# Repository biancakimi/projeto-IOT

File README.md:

# SmartGreenhouse LoRa — Sistema IoT de Monitoramento e Automação de Estufa Remota

-blue?style=flat-square&logo=espressif)

Sistema completo de **Internet das Coisas (IoT)** para monitoramento microclimático e controle automatizado de uma **estufa agrícola remota** sem cobertura Wi-Fi local. O projeto utiliza dois microcontroladores **ESP32-S3 LoRa 915 MHz (Heltec WiFi LoRa 32 V3)** operando em arquitetura *Nó Sensor/Atuador (ESP 1) $\leftrightarrow$ Gateway (ESP 2)*, integrados em tempo real via **Broker MQTT (`broker.emqx.io`)**, **API Serverless na Vercel (`/api/historico`)**, fluxos de automação em **Node-RED**, persistência histórica em **Banco de Dados Neon PostgreSQL** e uma **Aplicação Web de Gerenciamento Remoto**.

> **Universidade Federal de São Paulo (UNIFESP)** — Instituto de Ciência e Tecnologia (ICT - SJC)  
> **Disciplina:** Internet das Coisas (IdC) — Prof. Dr. Gabriel de Freitas Fernandes

---

## Sumário

1. [Visão Geral do Sistema](#visão-geral-do-sistema)
2. [Arquitetura de Comunicação](#arquitetura-de-comunicação)
3. [Funcionalidades e Modos de Operação](#funcionalidades-e-modos-de-operação)
   - [1. Modo Automático (Controle Local Resiliente)](#1-modo-automático-controle-local-resiliente)
   - [2. Modo Manual (Override Remoto pelo Site / Node-RED)](#2-modo-manual-override-remoto-pelo-site--node-red)
4. [Hardware e Pinagem (Nó Estufa — Heltec V3)](#hardware-e-pinagem-nó-estufa--heltec-v3)
5. [Protocolo de Mensagens (LoRa & MQTT)](#protocolo-de-mensagens-lora--mqtt)
   - [Pacotes LoRa (915 MHz)](#pacotes-lora-915-mhz)
   - [Tópicos MQTT](#tópicos-mqtt)
6. [Estrutura do Repositório](#estrutura-do-repositório)
7. [Fluxo de Trabalho Git e Automação de Pull Requests](#fluxo-de-trabalho-git-e-automação-de-pull-requests)
8. [Como Executar o Projeto](#como-executar-o-projeto)
9. [Integrantes e Divisão de Responsabilidades](#integrantes-e-divisão-de-responsabilidades)

---

## Visão Geral do Sistema

Estufas de cultivo frequentemente estão afastadas de pontos de acesso Wi-Fi. Para contornar essa limitação e garantir alta confiabilidade, o **SmartGreenhouse LoRa** organiza a solução em três camadas:

1. **Nó Estufa — ESP 1 (ESP32-S3 Heltec WiFi LoRa 32 V3 — Remoto):** Instalado na estufa sem necessidade de internet local. Realiza a leitura contínua de **luminosidade (LDR no GPIO 4)** e **temperatura e umidade do ar (DHT11 no GPIO 5)**, exibe o diagnóstico no **Display OLED SSD1306 integrado**, controla o ângulo da **persiana via 1 servomotor (GPIO 6)**, aciona **1 Módulo Relé de 4 Canais 5V (nos GPIOs 47, 48, 33 e 34)** (Ventoinha 5V de exaustão, iluminação de cultivo, bomba de irrigação e aquecedor) e sinaliza status localmente (**LEDs Verde/Vermelho com resistores de 1 kΩ e Buzzer**). Transmite telemetria via **LoRa 915 MHz** a cada 5s (e imediatamente após executar qualquer comando recebido do ESP 2) e mantém controle autônomo local (*fail-safe*).
2. **Nó Gateway — ESP 2 (ESP32-S3 Heltec WiFi LoRa 32 V3 — Central):** Localizado na sede com conexão Wi-Fi 2.4 GHz. Recebe os pacotes LoRa em 915 MHz vindos do ESP 1 (via transceptor Semtech SX1262), afere a qualidade do enlace de rádio (`RSSI` em dBm e `SNR` em dB) e encaminha os dados simultaneamente para o **Broker MQTT (`broker.emqx.io`)** e via **HTTPS POST para a API Serverless da Vercel (`/api/historico`)**. No sentido inverso, recebe ordens enviadas pelo Site Web ou Node-RED e as transmite imediatamente via **LoRa 915 MHz** para o ESP 1. Conta ainda com portal web local (`Gateway_LoRa_V3` $\rightarrow$ `http://192.168.4.1`) para configuração dinâmica de Wi-Fi/MQTT e suporte a **atualização remota de firmware (ArduinoOTA)**.
3. **Nuvem, Banco de Dados e Site Web:**
   * **API Serverless Vercel (`api/historico.js`) + Neon PostgreSQL:** Cria automaticamente as tabelas `historico_estufa` e `comandos_estufa`, armazena a série temporal completa de leituras/estados e enfileira comandos remotos para o Gateway.
   * **Node-RED (`nuvem_nodered/flows_estufa.json`):** Orquestra a ingestão dos pacotes MQTT, formata payloads para o banco SQL e disponibiliza botões de injeção de comandos.
   * **Site Web de Controle (`web/`):** Interface web responsiva hospedada na **Vercel** (e executável localmente), conectada em tempo real via **MQTT over WebSockets (`wss://broker.emqx.io:8084/mqtt`)** e integrada à API `/api/historico` para exibição de gráficos históricos (Chart.js) e tabela de registros.

---

## Arquitetura de Comunicação

```mermaid
flowchart LR
    subgraph Estufa["Nó Estufa (Heltec V3 Remota)"]
        direction TB
        LDR["Sensor LDR (GPIO 4)"] --> ESP_EST["ESP32-S3 Heltec V3\n+ OLED SSD1306"]
        DHT["Sensor DHT11 (GPIO 5)"] --> ESP_EST
        ESP_EST --> SERVO["1x Servomotor\n(Persiana 0°–180° - GPIO 6)"]
        ESP_EST --> RELES["1x Módulo Relé 4 Canais (5V)\n(CH1 Ventoinha P47 | CH2 Iluminação P48 |\nCH3 Irrigação P33 | CH4 Aquecedor P34)"]
        ESP_EST --> ALARME["LEDs Status + Buzzer (GPIO 40, 41, 42)"]
    end

    subgraph Enlace["Rádio LoRa 915 MHz"]
        RF(("Semtech SX1262\nP2P Bidirecional"))
    end

    subgraph Gateway["ESP 2: Nó Gateway (Heltec V3 Central)"]
        ESP_GW["ESP32-S3 Heltec V3\n(Bridge LoRa <-> MQTT & HTTPS\n+ Portal 192.168.4.1 + OTA)"]
    end

    subgraph Cloud["Nuvem & Gerenciamento Web"]
        BROKER["Broker MQTT EMQX\n(TCP 1883 / WSS 8084)"]
        API["Vercel Serverless API\n(/api/historico)"]
        NODERED["Node-RED\n(Ingestão + Automação)"]
        DB[("Neon PostgreSQL\n(Histórico em Nuvem)")]
        SITE["Site Web Responsivo\n(Vercel + Chart.js)"]
    end

    ESP_EST <==>|"Telemetria & Ordens"| RF
    RF <==>|"RSSI / SNR"| ESP_GW
    ESP_GW <==>|"Wi-Fi (MQTT)"| BROKER
    ESP_GW <==>|"HTTPS POST"| API
    API <==>|"SQL"| DB
    BROKER <==>|"Pub/Sub"| NODERED
    BROKER <==>|"WebSockets (WSS)"| SITE
    API <==>|"Histórico & Comandos"| SITE
```

---

## Funcionalidades e Modos de Operação

### 1. Modo Automático (Controle Local Resiliente)
O Nó Estufa avalia continuamente os sensores a cada ciclo curto (~600 ms para LDR e 2 s para DHT11) e atua autonomamente:

* **Controle do Servomotor da Persiana (GPIO 6) em Resposta à Luz (LDR):**
  * **Escuro / Tampando o LDR (`Luz < 25%`):** Persiana fecha em **`0°` (Fechada)** para isolamento térmico e **LIGA o Relé 2 (Iluminação de Cultivo)** para suplementação luminosa.
  * **Luz Ambiente Normal (`25% <= Luz <= 75%`):** Persiana abre em **`90°` (Aberta)** para máximo aproveitamento da luz solar e ventilação natural, **DESLIGANDO o Relé 2**.
  * **Sol Muito Forte / Lanterna no LDR (`Luz > 75%`):** Persiana inclina para **`160°` (Sombreamento)** para proteger as plantas contra insolação excessiva e queima de folhas.
* **Controle do Módulo Relé de 4 Canais 5V (Lado do Pino 47):**
  * **Canal 1 (`IN1`) — Ventoinha 5V (Exaustor / Refrigeração):** Liga quando `Temperatura > 28 °C` ou `Umidade > 80%`.
  * **Canal 2 (`IN2`) — Iluminação Artificial (Cultivo):** Liga automaticamente quando `Luz < 25%`.
  * **Canal 3 (`IN3`) — Bomba de Irrigação / Nebulização:** Liga quando `Umidade < 45%`.
  * **Canal 4 (`IN4`) — Aquecedor Térmico:** Liga quando `Temperatura < 18 °C`.
* **Alarme Audiovisual Local (Buzzer + LEDs):**
  * **LED Verde (GPIO 41):** Aceso contínuo durante operação normal.
  * **LED Vermelho (GPIO 40) + Buzzer (GPIO 42):** Acionados em caso de emergência climática (`Temperatura >= 35 °C`), forçando a Ventoinha (Relé 1) a ligar e transmitindo status de alerta via LoRa/MQTT.
  * O Buzzer também emite bipes curtos de aviso ao movimentar a persiana.

### 2. Modo Manual (Override Remoto pelo Site / Node-RED)
Através do painel web ou do Node-RED, o operador pode assumir o controle a qualquer momento:
* Ajuste do ângulo da persiana ($0^\circ$ a $180^\circ$) por *slider* ou atalhos rápidos (*Fechar 0°*, *Meia-Luz 45°*, *Abrir 90°*, *Sombra 160°*).
* Acionamento manual e individual dos 4 Relés (Ventoinha, Iluminação de Cultivo, Irrigação, Aquecedor).
* Inversão rápida da lógica de disparo dos relés (`Ativo em HIGH` $\leftrightarrow$ `Ativo em LOW`).
* Silenciamento temporário (*Mute*) ou teste manual do Buzzer.
* Reprogramação remota dos limiares de acionamento do modo automático.

---

## Hardware e Pinagem (Nó Estufa — Heltec V3)

O circuito do Nó Estufa foi dimensionado para a placa **Heltec WiFi LoRa 32 V3 (ESP32-S3)** com transceptor **Semtech SX1262 (915 MHz)** e **Display OLED SSD1306 integrado**.

| Periférico / Sensor | Pino na Heltec V3 | Tipo de Interface | Função no Sistema |
| :--- | :---: | :---: | :--- |
| **LoRa Semtech SX1262** | `NSS=8, SCK=9, MOSI=10, MISO=11, RST=12, BUSY=13, DIO1=14` | SPI Dedicado | Comunicação rádio LoRa 915 MHz |
| **Display OLED SSD1306 (128x64)** | `SDA=17, SCL=18, RST=21, Vext=36` | I2C Interno | Exibição local de IP, sensores, persiana, relés e LoRa |
| **LED Onboard Branco** | `GPIO 35` | Saída Digital | Indicação de atividade dos relés e pacotes LoRa |
| **Botão PRG / BOOT** | `GPIO 0` | Entrada com Pull-up | Alterna manualmente entre modo AUTO e MANUAL na bancada |
| **Sensor LDR (Luminosidade)** | `GPIO 4` | Entrada Analógica (ADC1) | Divisor de tensão com resistor de $10\text{ k}\Omega$ para medição de luz (%) |
| **Sensor DHT11 (Temp. e Umidade)** | `GPIO 5` | Digital One-Wire | Medição de temperatura (°C) e umidade relativa (%) |
| **Servomotor da Persiana** | `GPIO 6` | Saída PWM (50 Hz) | Controle do ângulo das aletas da persiana ($0^\circ$ a $180^\circ$) |
| **Relé 4 Canais (`CH1`) — Ventoinha 5V** | `GPIO 47` | Saída Digital | Aciona a **Ventoinha 5V** (Exaustor no contato `NA` do canal 1) |
| **Relé 4 Canais (`CH2`) — Iluminação** | `GPIO 48` | Saída Digital | Aciona a **Iluminação Artificial** (Cultivo no canal 2) |
| **Relé 4 Canais (`CH3`) — Irrigação** | `GPIO 33` | Saída Digital | Aciona a **Bomba de Irrigação / Válvula** (canal 3) |
| **Relé 4 Canais (`CH4`) — Aquecedor** | `GPIO 34` | Saída Digital | Aciona o **Aquecedor Térmico** (canal 4) |
| **Buzzer de Alerta** | `GPIO 42` | Saída Digital | Alarme sonoro local de emergência e movimentação |
| **LED Status Verde** | `GPIO 41` | Saída Digital | Indicação visual de operação normal |
| **LED Status Vermelho** | `GPIO 40` | Saída Digital | Indicação visual de alarme crítico |

> **Nota de Alimentação dos 4 Relés e GND Comum:** Os módulos Relé de 5V devem ter `VCC` alimentado em `+5V` e o pino **`GND` obrigatoriamente interligado ao `GND` do ESP32 (Terra Comum)** para que o sinal lógico de `3.3V` seja referenciado corretamente. Na borneira de potência de cada relé, o `+5V` entra no terminal `COM` e o fio positivo da carga (ex.: Ventoinha) sai do terminal **`NA` (Normalmente Aberto)**.

---

## Protocolo de Mensagens (LoRa & MQTT)

### Pacotes LoRa (915 MHz)
* **Telemetria (ESP 1 Estufa $\rightarrow$ ESP 2 Gateway a cada 5s e após comandos):**
  ```json
  {"id":"EST01","seq":301,"t":28.9,"h":48.0,"l":83,"adc":3421,"srv":160,"r":[1,0,0,0],"al":0,"buz":1,"inv":0,"dht":1,"m":"AUTO"}
  ```
  *(Onde: `t` = Temp °C, `h` = Umidade %, `l` = Luz %, `adc` = Leitura ADC bruta do LDR, `srv` = Ângulo do servo, `r` = Estado dos 4 Relés R1..R4 nos pinos 47/48/33/34, `al` = Alarme, `buz` = Buzzer ativo, `inv` = Lógica invertida, `dht` = Status do DHT11, `m` = Modo).*
* **Comando de Atuação (ESP 2 Gateway $\rightarrow$ ESP 1 Estufa sob demanda):**
  ```json
  {"target":"EST01","cmd":"SET","m":"MAN","srv":45,"ch":0,"state":1,"buz":1,"inv":0}
  ```
* **Configuração de Limiares (ESP 2 Gateway $\rightarrow$ ESP 1 Estufa):**
  ```json
  {"target":"EST01","cmd":"CFG","tMax":28.0,"tMin":18.0,"tCrit":35.0,"hMin":45.0,"lMin":25,"lMax":75}
  ```

### Tópicos MQTT
> Broker padrão configurado: `broker.emqx.io` (`TCP 1883` no ESP 2 e `WSS 8084` no Site Web).
| Tópico | Direção | Descrição |
| :--- | :---: | :--- |
| `unifesp/iot/estufa/telemetria` | `ESP 2 Gateway -> Nuvem` | Payload JSON completo da estufa acrescido de `rssi`, `snr`, `gwId` e `gwRx` |
| `unifesp/iot/estufa/gateway/status` | `ESP 2 Gateway -> Nuvem` | Heartbeat do Gateway com IP Wi-Fi, RSSI Wi-Fi, contadores LoRa/Vercel e uptime |
| `unifesp/iot/estufa/comando` | `Site / Nuvem -> ESP 2` | Comando JSON unificado (`SET`, `CFG` ou `PING`) encaminhado via LoRa ao ESP 1 |
| `unifesp/iot/estufa/comando/modo` | `Site / Nuvem -> ESP 2` | Define o modo de operação (`"AUTO"` ou `"MAN"`) |
| `unifesp/iot/estufa/comando/persiana` | `Site / Nuvem -> ESP 2` | Define o ângulo da persiana (`0` a `180`) |
| `unifesp/iot/estufa/comando/reles` | `Site / Nuvem -> ESP 2` | Aciona individualmente um dos 4 Relés (`{"ch":0,"state":1}`) |
| `unifesp/iot/estufa/comando/config` | `Site / Nuvem -> ESP 2` | Reconfigura setpoints de automação remotamente |

---

## Estrutura do Repositório

```text
projeto-IOT/
├── .github/
│   ├── workflows/
│   │   ├── pr-code-review.yml          # CI e Code Review Automatizado nos Pull Requests
│   │   └── enforce-branch-protection.yml
│   └── PULL_REQUEST_TEMPLATE.md
├── .githooks/                          # Hooks Git que bloqueiam commits diretos em main/develop
│   ├── pre-commit
│   └── pre-push
├── api/
│   └── historico.js                    # API Serverless Vercel (GET/POST Neon PostgreSQL + Fila de Comandos)
├── firmware/
│   ├── no_estufa_lora/
│   │   └── no_estufa_lora.ino          # Firmware do ESP 1: Nó Estufa (Heltec V3 + 4 Relés 47/48/33/34 + Servo + Sensores)
│   ├── no_gateway_lora_mqtt/
│   │   └── no_gateway_lora_mqtt.ino    # Firmware do ESP 2: Nó Gateway (Heltec V3 + LoRa <-> MQTT/Vercel + OTA)
│   └── teste_hardware_lora_wifi_oled/
│       └── teste_hardware_lora_wifi_oled.ino # Diagnóstico completo de bancada (SX1262 + OLED + AP)
├── web/                                # Site de Gerenciamento Remoto (Vercel + MQTT over WebSockets)
│   ├── index.html
│   ├── css/
│   │   └── styles.css
│   └── js/
│       └── app.js
├── nuvem_nodered/
│   ├── flows_estufa.json               # Fluxos exportados do Node-RED
│   └── schema_banco.sql                # Script SQL das tabelas historico_estufa e comandos_estufa
├── pci_hardware/
│   ├── README.md
│   └── lista_materiais_BOM.md          # Lista de componentes da PCI (2x Módulos Relé Duplos, etc.)
├── encapsulamento_3d/
│   └── README.md                       # Modelos 3D (.STL) do encapsulamento
├── docs/
│   └── evidencias/
│       └── README.md                   # Fotos e vídeos de validação
├── scripts/
│   └── configure-branch-protection.ps1 # Script para ativar hooks e proteção de branch
├── package.json                        # Dependências da API Serverless (@neondatabase/serverless)
├── vercel.json                         # Regras de roteamento da Vercel para /web e /api/historico
└── README.md
```

---

## Fluxo de Trabalho Git e Automação de Pull Requests

Este repositório conta com automação de governança (`.githooks/` e **GitHub Actions**) que **bloqueia commits diretos nas branches `main` e `develop`**. Todo desenvolvimento deve seguir o fluxo abaixo:

1. **Ative os hooks locais após clonar (uma única vez):**
   ```powershell
   ./scripts/configure-branch-protection.ps1
   ```
2. **Crie uma branch separada a partir da `develop`:**
   ```bash
   git checkout develop
   git pull origin develop
   git checkout -b feature/minha-funcionalidade
   ```
3. **Faça seus commits e envie sua branch para o GitHub:**
   ```bash
   git add .
   git commit -m "feat: implementa controle do servo via LDR"
   git push -u origin feature/minha-funcionalidade
   ```
4. **Abra um Pull Request para a branch `develop`:**
   * O workflow **`Automated Code Review & Validation`** executará automaticamente a verificação de código e comentará o relatório no PR.
   * **Requisito de Merge:** O PR só poderá ser integrado à `develop` após passar no Code Review automatizado **e** receber a aprovação (**Approve**) de pelo menos **1 outro integrante do grupo**.

---

## Como Executar o Projeto

1. **Bibliotecas Necessárias (Arduino IDE):**
   * No Gerenciador de Bibliotecas da Arduino IDE, instale:
     * **`RadioLib`** (por Jan Gromes) — suporte ao chip LoRa Semtech SX1262
     * **`Adafruit SSD1306`** e **`Adafruit GFX Library`** — display OLED integrado
     * **`DHT sensor library`** (por Adafruit) e **`Adafruit Unified Sensor`**
     * **`ESP32Servo`** (por Kevin Harrington / John K. Bennett)
     * **`ArduinoJson`** (por Benoit Blanchon)
     * **`PubSubClient`** (por Nick O'Leary)
2. **Gravação do Firmware:**
   * Em **Ferramentas $\rightarrow$ Placa**, selecione **`Heltec WiFi LoRa 32(V3)`** (ou `ESP32S3 Dev Module`).
   * Grave `no_estufa_lora.ino` no **ESP 1 (Estufa)** e `no_gateway_lora_mqtt.ino` no **ESP 2 (Gateway)**.
3. **Painéis Web de Validação e Configuração Local na Bancada (`192.168.4.1`):**
   * **ESP 1 (Estufa):** Cria a rede Wi-Fi **`Estufa_LoRa_V3`** (senha: **`12345678`**). Acessando **`http://192.168.4.1`**, é possível testar localmente o servomotor, os 2 módulos Relé duplos (`P47`, `P48`, `P33`, `P34`) e os sensores.
   * **ESP 2 (Gateway):** Cria a rede Wi-Fi **`Gateway_LoRa_V3`** (senha: **`12345678`**). Acessando **`http://192.168.4.1`**, é possível configurar o nome/senha do Wi-Fi 2.4 GHz da bancada, o host do Broker MQTT e a URL da Vercel sem precisar regravar o código.
4. **Banco de Dados Neon PostgreSQL, Vercel e Node-RED (`api/` e `nuvem_nodered/`):**
   * Na Vercel, conecte o banco **Neon PostgreSQL** (variável `DATABASE_URL`). O endpoint `/api/historico` criará automaticamente as tabelas `historico_estufa` e `comandos_estufa` (também documentadas em `nuvem_nodered/schema_banco.sql`).
   * No Node-RED, importe o arquivo `flows_estufa.json` para monitorar os tópicos MQTT em `broker.emqx.io`.
5. **Site de Gerenciamento Remoto (`web/`):**
   * Acesse pela URL da **Vercel** (ou abra `web/index.html` diretamente no navegador) para visualizar os sensores, o link LoRa (`RSSI`/`SNR`) e os gráficos históricos em tempo real, além de controlar remotamente a persiana e os 4 relés do ESP 1 através do ESP 2.

---

## Integrantes e Divisão de Responsabilidades

| Frente / Etapa do Projeto | Descrição das Entregas sob Responsabilidade | Nome do(a) Integrante | RA | GitHub |
| :--- | :--- | :---: | :---: | :---: |
| **1. Hardware, Circuito e PCI** | Validação em protoboard, esquemático elétrico, confecção da Placa de Circuito Impresso (PCI) e modelagem do encapsulamento 3D | *[Inserir Nome]* | *[Inserir RA]* | `@usuario` |
| **2. Firmware Nó Estufa & LoRa** | Código do ESP32 LoRa #1 (`no_estufa_lora.ino`), leitura de sensores (DHT11/LDR), controle do Servo/4 Relés/Buzzer e protocolo LoRa 915 MHz | *[Inserir Nome]* | *[Inserir RA]* | `@usuario` |
| **3. Firmware Nó Gateway & OTA** | Código do ESP32 LoRa #2 (`no_gateway_lora_mqtt.ino`), ponte LoRa $\leftrightarrow$ Wi-Fi/MQTT, leitura de RSSI/SNR e atualização remota (OTA) | *[Inserir Nome]* | *[Inserir RA]* | `@usuario` |
| **4. Nuvem (Node-RED), Banco & Web** | Fluxos do Node-RED (`flows_estufa.json`), banco de dados histórico (`schema_banco.sql`) e site de controle remoto (`web/`) | *[Inserir Nome]* | *[Inserir RA]* | `@usuario` |

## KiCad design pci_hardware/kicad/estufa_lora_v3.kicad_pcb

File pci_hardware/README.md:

# Projeto de Placa de Circuito Impresso (PCI) — `pci_hardware/`

Esta pasta armazena os artefatos completos referentes à etapa de **Projeto e Confecção da Placa de Circuito Impresso (PCI)** do Nó Estufa (**Heltec WiFi LoRa 32 V3**), elaborados no **KiCad 10.0** seguindo rigorosamente o padrão das videoaulas da disciplina (**Prof. Dr. Gabriel de Freitas Fernandes**):

* [`kicad/estufa_lora_v3.kicad_pro`](kicad/estufa_lora_v3.kicad_pro): Arquivo principal do projeto KiCad.
* [`kicad/estufa_lora_v3.kicad_sch`](kicad/estufa_lora_v3.kicad_sch): Diagrama esquemático elétrico completo seguindo o padrão da disciplina:
  * Símbolos customizados na biblioteca local [`kicad/heltec_iot.kicad_sym`](kicad/heltec_iot.kicad_sym): **`U1` (`Heltec_WiFi_LoRa_32_V3`)** com a pinagem física oficial completa (2x18 pinos) e **`J2` (`Modulo_Rele_4_Canais_5V`)** representando explicitamente as 4 portas/canais (`K1` Ventoinha, `K2` Iluminação, `K3` Irrigação e `K4` Aquecedor).
  * Uso de símbolos de aterramento **`GND` (`power:GND`)**, etiquetas globais (**`global_label`**) para barramentos e sinais dos conectores (`5V`, `3V3`, `RELE1_P47`, `RELE2_P48`, `RELE3_P33`, `RELE4_P34`, `LDR_P4`, `DHT11_P5`, `SERVO_P6`, `LED_VERM_P40`, `LED_VERDE_P41`, `BUZZER_P42`) e ligação direta por fios dentro de cada subcircuito.
  * **Fonte externa de `5V` (`J1` + capacitor `C1` de `100uF`)** alimentando diretamente o **pino `5V` do Heltec V3 (`U1`)**, o **Módulo Relé de 4 Canais (`J2`, conector 1x06 pinos)** e o **Servomotor (`J3`)**.
  * **Resistores de `1k` (`R3`, `R4`)** nos LEDs de status (`D1` Verde e `D2` Vermelho), divisor de tensão do **LDR com resistor de `10k` (`R1`, `R2`)** e **DHT11 (`J4`) ligado diretamente ao `GPIO 5` (sem resistor externo)**.
  * Nota de documentação de projeto detalhando decisões de hardware, autores, revisão e data.
* [`kicad/estufa_lora_v3.kicad_pcb`](kicad/estufa_lora_v3.kicad_pcb): Layout da Placa de Circuito Impresso (**Face Única `F.Cu` + Plano Terra `GND`** sem alívio térmico e com espaçamento de `0.8 mm` / trilhas de `1.0 mm` para potência e `0.5 mm` para sinal, otimizado para a fresadora CNC do laboratório da UNIFESP, aprovado no DRC com **0 violações e 0 itens desconectados**).
* [`kicad/esquematico_estufa_lora.pdf`](kicad/esquematico_estufa_lora.pdf): PDF do esquemático elétrico pronto para impressão/apresentação.
* [`kicad/layout_pci_estufa_lora.pdf`](kicad/layout_pci_estufa_lora.pdf): PDF do layout das trilhas e Plano Terra da PCI.
* `kicad/gerbers/`: Arquivos industriais Gerber (`.gtl`, `.gbl`, `.gto`, `.gts`, `.gm1`) e furação Excellon (`.drl`) prontos para fabricação da PCI.
* [`lista_materiais_BOM.md`](lista_materiais_BOM.md): Lista de componentes (Bill of Materials) atualizada.

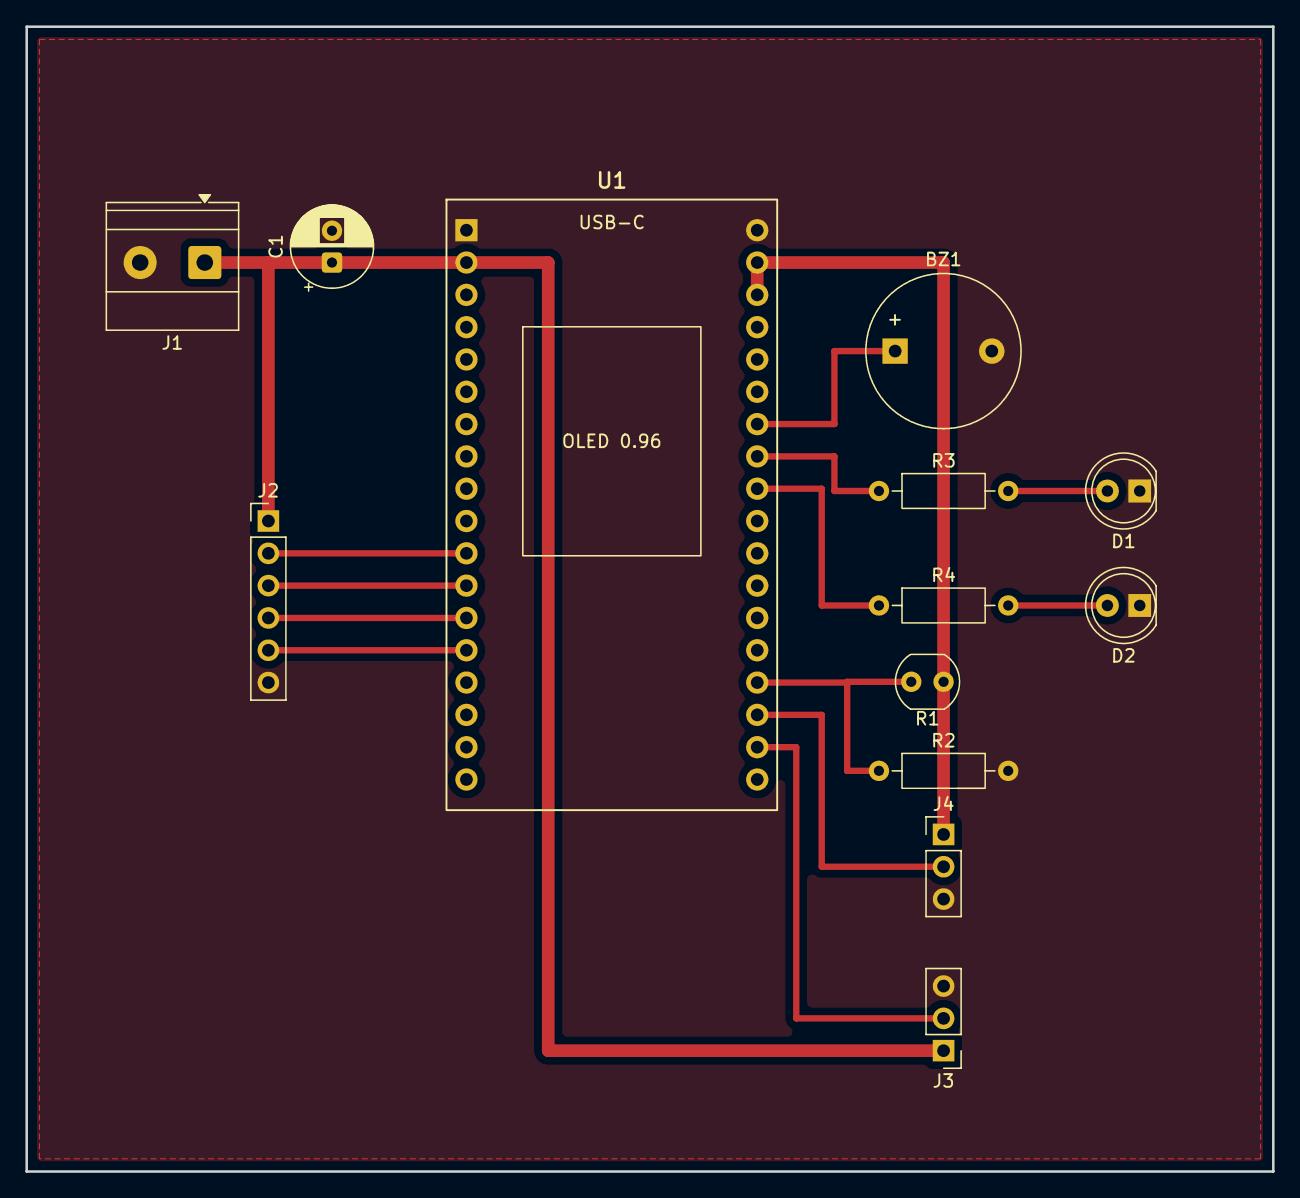
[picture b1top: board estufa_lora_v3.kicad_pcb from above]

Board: 2 copper layers, 98.0 x 90.0 mm, 13 parts (0 on the bottom side), 15 nets.

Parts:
BZ1: Buzzer; Buzzer_12x9.5RM7.6
C1: 100uF; CP_Radial_D6.3mm_P2.50mm
D1: LED_Verde; LED_D5.0mm
D2: LED_Vermelho; LED_D5.0mm
J1: Fonte_5V_GND; TerminalBlock_Phoenix_MKDS-1,5-2-5.08_1x02_P5.08mm_Horizont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
J2: Rele_4_Canais; PinHeader_1x06_P2.54mm_Vertical
J3: Servo_P6; PinHeader_1x03_P2.54mm_Vertical
J4: DHT11; PinHeader_1x03_P2.54mm_Vertical
R1: LDR; R_LDR_4.9x4.2mm_P2.54mm_Vertical
R2: 10k; R_Axial_DIN0207_L6.3mm_D2.5mm_P10.16mm_Horizontal
R3, R4: 1k; R_Axial_DIN0207_L6.3mm_D2.5mm_P10.16mm_Horizontal
U1: Heltec_WiFi_LoRa_32_V3

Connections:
3V3: J4.1, R1.1, U1.20, U1.21
5V: C1.1, J1.1, J2.1, J3.1, U1.2
BUZZER_P42: BZ1.1, U1.25
DHT11_P5: J4.2, U1.34
GND: BZ1.2, C1.2, D1.1, D2.1, J1.2, J2.6, J3.3, J4.3, R2.2, U1.1, U1.19
LDR_P4: R1.2, R2.1, U1.33
LED_VERDE_P41: R3.1, U1.26
LED_VERM_P40: R4.1, U1.27
N_LED_VERDE: D1.2, R3.2
N_LED_VERM: D2.2, R4.2
RELE1_P47: J2.4, U1.13
RELE2_P48: J2.5, U1.14
RELE3_P33: J2.3, U1.12
RELE4_P34: J2.2, U1.11
SERVO_P6: J3.2, U1.35
